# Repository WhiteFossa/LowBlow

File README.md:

# Project LowBlow - Advanced programmable cooler controller

Open source and hardware (GPLv3+) advanced programmable cooler controller.

## Features
- Automatically learns cooler characteristics: at power on it determines minimal voltage at one cooler starts, minimal RPMs and maximal RPMs, so you don't need to adjust temperature-to-RPMs settings for different coolers;
- Cooler speed is being controlled via RPMs loopback (using tachometer), so 50% RPMs will actually be 50% RPMs, not just a half of power voltage. In addition if something affects cooler RPMs, voltage will be adjusted to keep desired RPMs.
- Control tool to configure temperature-to-RPMs curve. Using this tool you can set up curve via changing values in table, view how curve looks and finally generate EEPROM HEX file to flash it into controller.

Control tool screenshot:

## How to build/flash/use etc
Each project directory (i.e. Hardware, Firmware and Control Tool) contain README file with instructions.

## License
Everything in this project (except Intel HEX library) are distributed under GPLv3 or later version license.

Intel HEX library is written by  Kimmo Kulovesi, distributed under MIT license and can be downloaded from here: https://github.com/arkku/ihex

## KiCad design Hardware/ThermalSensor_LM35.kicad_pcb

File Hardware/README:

Project LowBlow control tool.
https://github.com/WhiteFossa/LowBlow

Hardware README

I. Desolder C8 before flashing (flashing will be unsuccessfull if not desoldered) and solder back before using (without C8 tachometer signal wouldn't be clear and device may not work).

II. Project depends on my components for KiCAD library, you can download it here: https://github.com/WhiteFossa/fossas_kicad_lib

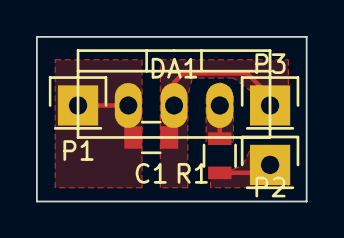
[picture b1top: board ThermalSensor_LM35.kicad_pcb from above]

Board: 2 copper layers, 15.0 x 9.1 mm, 6 parts (0 on the bottom side), 4 nets.

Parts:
C1: 0.1uF; C_0805
DA1: LM35_-_TO-220; TO-220_Neutral123_Vertical
P1: VCC; Pin_Header_Straight_1x01
P2: OUT; Pin_Header_Straight_1x01
P3: GND; Pin_Header_Straight_1x01
R1: 2k; R_0805

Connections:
unnamed: C1.1, DA1.1, P1.1
unnamed: C1.2, DA1.2, P3.1
unnamed: DA1.3, R1.2
unnamed: P2.1, R1.1

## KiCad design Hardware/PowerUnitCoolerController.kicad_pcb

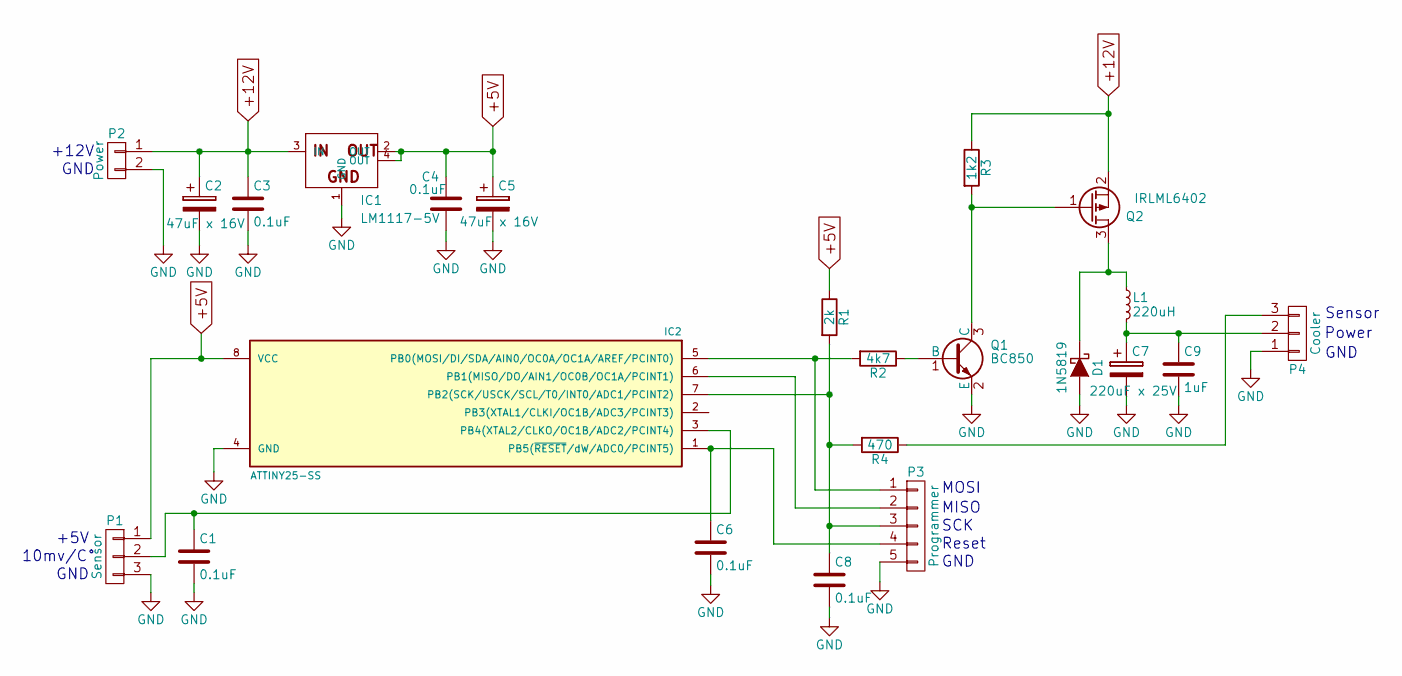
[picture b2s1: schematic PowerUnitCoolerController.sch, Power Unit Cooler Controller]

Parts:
C1, C3, C4, C6, C8: 0.1uF; C_0805
C2, C5: 47uF x 16V; TantalC_SizeV_EIA-7343
C7: 220uF x 25V; c_elec_8x10.5
C9: 1uF; C_0805
D1: 1N5819; MiniMELF_Handsoldering
IC1: LM1117-5V; SOT-223
IC2: ATTINY25-SS; SOIJ-8_5.3x5.3mm_Pitch1.27mm
L1: 220uH; Neosid_Inductor_SM-NE56_SMD2220
P1: Sensor; Pin_Header_Straight_1x03
P2: Power; Pin_Header_Straight_1x02
P3: Programmer; Pin_Header_Straight_1x05
P4: Cooler; Pin_Header_Straight_1x03
Q1: BC850; SOT-23
Q2: IRLML6402; SOT-23
R1: 2k; R_0805
R2: 4k7; R_0805
R3: 1k2; R_0805
R4: 470; R_0805

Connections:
+5V: C4.1, C5.1, IC1.2 (OUT), IC1.4 (OUT), IC2.8 (VCC), P1.1, R1.1
+12V: C2.1, C3.1, IC1.3 (IN), P2.1, Q2.2 (S), R3.1
GND: C1.2, C2.2, C3.2, C4.2, C5.2, C6.2, C7.2, C8.2, C9.2, D1.2 (A), IC1.1 (GND), IC2.4 (GND), P1.3, P2.2, P3.5, P4.1, Q1.2 (E)
unnamed: C1.1, IC2.3 (PB4(XTAL2/CLKO/OC1B/ADC2/PCINT4)), P1.2
unnamed: C6.1, IC2.1 (PB5(~RESET~/dW/ADC0/PCINT5)), P3.4
unnamed: C7.1, C9.1, L1.2, P4.2
unnamed: C8.1, IC2.7 (PB2(SCK/USCK/SCL/T0/INT0/ADC1/PCINT2)), P3.3, R1.2, R4.2
unnamed: D1.1 (K), L1.1, Q2.3 (D)
unnamed: IC2.5 (PB0(MOSI/DI/SDA/AIN0/OC0A/OC1A/AREF/PCI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), P3.1, R2.2
unnamed: IC2.6 (PB1(MISO/DO/AIN1/OC0B/OC1A/PCINT1)), P3.2
unnamed: P4.3, R4.1
unnamed: Q1.1 (B), R2.1
unnamed: Q1.3 (C), Q2.1 (G), R3.2

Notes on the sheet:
Sensor
Power
GND
+12V
10mv/C°
+5V
MOSI
MISO
SCK
Reset

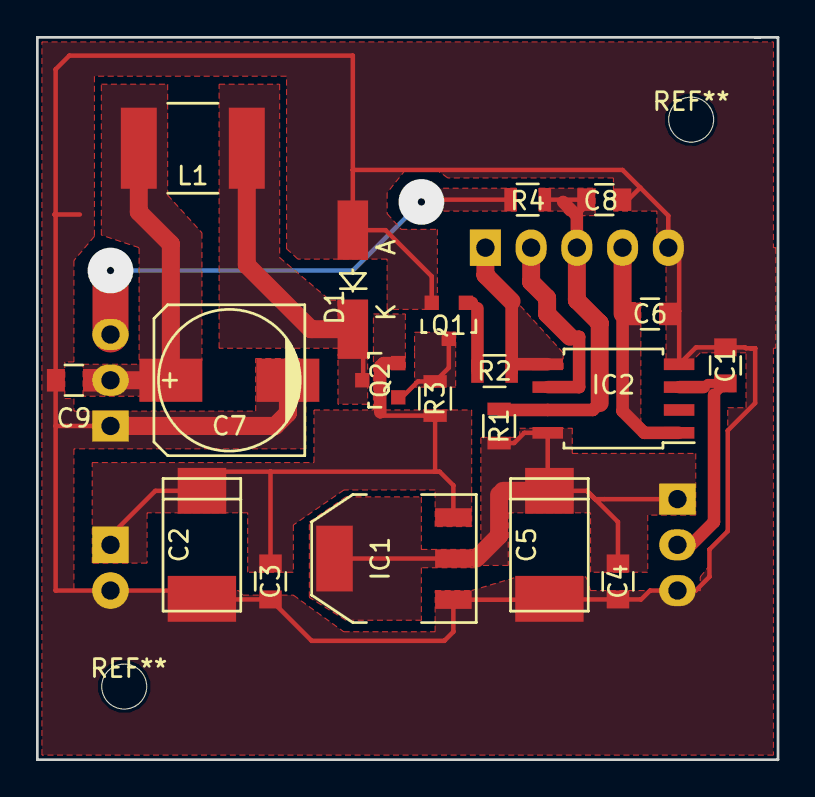
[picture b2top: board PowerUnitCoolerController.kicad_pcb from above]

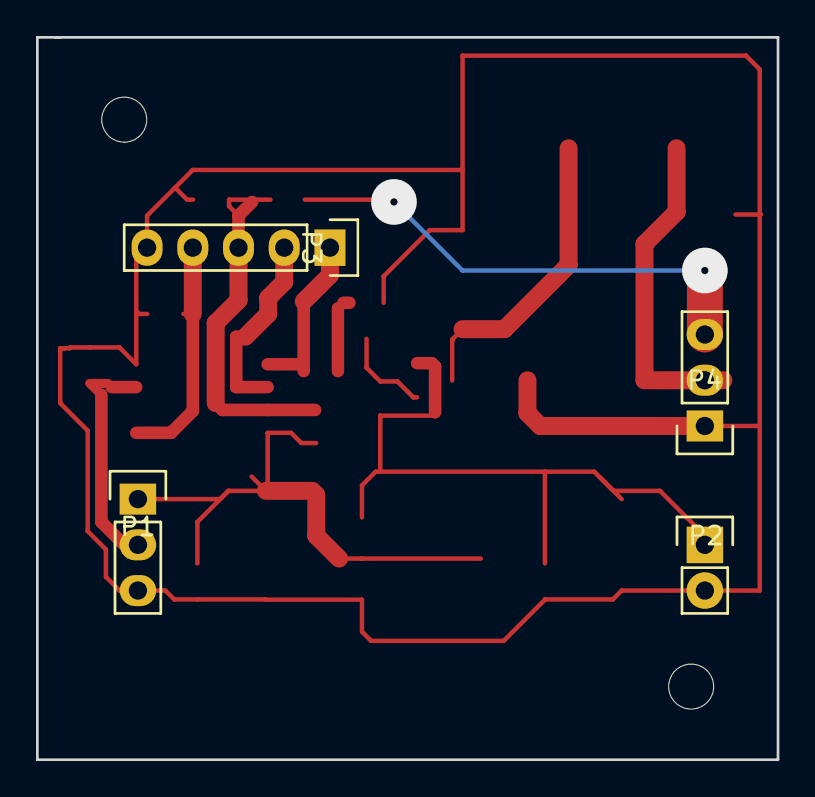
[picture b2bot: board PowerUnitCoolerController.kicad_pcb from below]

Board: 2 copper layers, 41.1 x 40.1 mm, 23 parts (4 on the bottom side), 13 nets.

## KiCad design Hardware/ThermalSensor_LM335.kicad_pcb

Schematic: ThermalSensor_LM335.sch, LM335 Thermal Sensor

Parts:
C1: 0.1uF; C_0805
DA1: LM335; TO-92_Molded_Narrow_Oval
P1: VCC; Pin_Header_Straight_1x01
P2: OUT; Pin_Header_Straight_1x01
P3: GND; Pin_Header_Straight_1x01
R1: 4k7; R_0805
R2: 10k; R_0805
R3: 20k; R_0805

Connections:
unnamed: C1.1, P1.1, R1.1
unnamed: C1.2, DA1.3, P3.1, R3.2
unnamed: DA1.2, R1.2, R2.1
unnamed: P2.1, R2.2, R3.1

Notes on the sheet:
6.(6) mV/°K 0°C -> 1.82V 100°C -> 2.49V

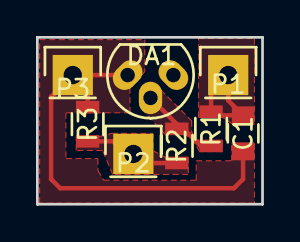
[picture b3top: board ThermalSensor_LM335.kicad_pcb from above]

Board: 2 copper layers, 12.5 x 9.3 mm, 8 parts (0 on the bottom side), 4 nets.

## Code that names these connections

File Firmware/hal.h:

/*
	This file is part of Power Unit Cooler Controller firmware.

	Power Unit Cooler Controller firmware is free software:
	you can redistribute it and/or modify it under the terms of the
	GNU General Public License as published by the Free Software
	Foundation, either version 3 of the License, or (at your option)
	any later version.

	Power Unit Cooler Controller firmware is distributed in the hope
	that it will be useful, but WITHOUT ANY WARRANTY; without even
	the implied warranty of MERCHANTABILITY or FITNESS FOR A
	PARTICULAR PURPOSE.  See the GNU General Public License for more
	details.

	You should have received a copy of the GNU General Public License
	along with Notebook Cooler Controller firmware.

	If not, see <http://www.gnu.org/licenses/>.

	-------------------------------------------------------------------------

	hal.h

	Hardware abstraction layer header file.

	Part of "LowBlow" project.

	Created 2016/02/07 by White Fossa, also known as Artyom Vetrov.

	Feel free to contact: whitefossa@gmail.com

	Repository: https://github.com/WhiteFossa/LowBlow

	If repository above is not available, try my LiveJournal:
	fossa-white.livejournal.com

	or as last measure try to search for #WhiteFossa hashtag.

	-------------------------------------------------------------------------
 */

#ifndef HAL_H_
#define HAL_H_

/**
 * Hardware:
 *
 *                             ATTINY25
 *                           +----__----+
 * RESET (PB5)          ->---| 1      8 |-----     VCC
 * NOT CONNECTED		->---| 2      7 |---<-     TACHO	(INT0/PB2)
 * TSENS (ADC2/PB4)     ->---| 3      6 |---<-     NOT CONNECTED
 * GND                  -----| 4      5 |--->-     PWM		(PB0/OC0A)
 *                           +----------+
 *
 * Directions:
 * PIN		DIR		DDRB
 *
 * PB0		OUT		1
 * PB1		IN		0
 * PB2		IN		0
 * PB3		IN		0
 * PB4		IN		0
 * PB5		IN		0
 *
 *
 * We can use two kinds on thermal sensors:
 *
 * 1) LM35 in direct mode, i.e. 10mV/°C. Uout=0.01*t°. Uncomment USE_LM35_SENSOR if you are using it. ADC will use 1.1V reference,
 * 10-bit mode, so ADC = 9.(309)*t°.
 *
 *   t °C		U V		ADC
 *   0			0		0
 *   100		1		233
 *
 * 233 steps per 100°C
 *
 * 2) LM335 with 2/3 divider, i.e. 6.(6)mV/°K. Uout=2*(t°+273.15)/300. ADC will use 2.56V reference, 10-bit moide. ADC=2.(6)*t°+728.4
 *
 *   t °C		U V		ADC
 *   0		   1.821	728
 *   100       2.487	995
 *
 * 267 steps per 100°C
 *
 * t° is temperature in Celsius.
 */

/**
 * !!!!!!!!!!!!!!!!!!!!!!!!!!!!!!!!!!!!!!!!!!!!!!!!!!
 * !!!!!!! UNCOMMENT IT IF LM35 SENSOR USED !!!!!!!!!
 * !!!!!!!!!!!!!!!!!!!!!!!!!!!!!!!!!!!!!!!!!!!!!!!!!!
 * #define USE_LM35_SENSOR
 */


/* AVR Libc includes*/
#include <avr/io.h> /* Common */
#include <avr/wdt.h> /* Watchdog timer */
#include <avr/interrupt.h> /* Interrupts support */
#include <util/delay_basic.h> /* Basic delays */

/* Macros */


/* Get cooler duty cycle */
#define hal_get_cooler_duty_cycle() OCR0A


/* End of macros */

/* Constants */

/**
 *  MCU Frequency
 */
#define F_CPU 8000000UL

/** !!!!!!!!!!!!!!!!!!!!!!!!!!!!!!!!!!!!!!!!!!!!!!!!!!!!!!!!!!
 *  !!PORTS DIRECTIONS - WRONG SETTINGS WILL DAMAGE HARDWARE!!
 *  !!!!!!!!!!!!!!!!!!!!!!!!!!!!!!!!!!!!!!!!!!!!!!!!!!!!!!!!!!
 */
#define HAL_PORTB_DIR 0b00000001

/**
 * Port, where cooler connected
 */
#define HAL_COOLER_PORT PORTB

/**
 * Cooler connected here
 */
#define HAL_COOLER_PIN 0x00 /* PB0 */

/**
 *  Watchdog timeout interval
 */
#define HAL_WDT_INTERVAL WDTO_2S

/**
 * Minimal possible duty cycle (set cycle to it to stop cooler).
 */
#define HAL_MIN_DUTY_CYCLE 0x00

/**
 * Maximal possible duty cycle
 */
#define HAL_MAX_DUTY_CYCLE 0xFF

/* This number of Timer1 overflows is near equal to 1 second
 * clock = 8.0 MHz, prescaler 16384, overflow occurs 8000000 / (16384 * 256) ~ 2 times per second.
 */
#define HAL_TIMER1_OVERFLOWS_PER_SECOND 2

/**
 * Number of bits, to what hal_adc_accumulator need to be shifted left to get hal_temperature.
 */
#define HAL_ADC_RESULT_SHIFT_BITS 8

/**
 * How many ADC measurements will be averaged to get temperature MINUS ONE (to keep it within uint8_t)
 */
#define HAL_ADC_NUM_OF_MEASUREMENTS (1 << HAL_ADC_RESULT_SHIFT_BITS) - 1

/* Flags */

/**
 *  Raised on exit from hal_second_tick() function. Can be used to know that new tachometer measurement completed
 */
#define HAL_F0_JUST_TICKED 0

/* End of flags */

/* End of constants */



/* Variables */

/**
 * Variable for different flags, related to HAL. By default all flags are cleared (zeros).
 */
volatile uint8_t hal_flags0;

/* Loaded with HAL_TIMER1_OVERFLOWS_PER_SECOND on hal_second_tick() and decreases on every Timer1 interrupt. If this
 * variable equals 0 AFTER decrement then new second passed, calling hal_second_tick()
 */
volatile uint16_t hal_timer1_overflows_number;

/** Increases with every pulse from tachometer (i.e. INT0), gets copied to hal_tacho when hal_second_tick() called and
 * set to 0. For most coolers 2 pulses from tachometer = 1 revolution, but as I heard some coolers with 8 pulses per
 * revolution exists.
 * With uint16_t, 8 pulses per revolution and 1 second interval maximal allowed RPM will be 65535 * 60 / 8 = 491512.5
 */
volatile uint16_t hal_tacho_counter;

/** Number of tachometer pulses per second
 */
volatile uint16_t hal_tacho;

/**
 * ADC measurements accumulating here before being averaged and placed into hal_temperature.
 */
volatile uint32_t hal_adc_accumulator;

/**
 * Counter to count ADC measurements.
 */
volatile uint8_t hal_adc_avg_counter;


/**
 * Averaged ADC measurement, i.e. temperature.
 */
volatile uint16_t hal_temperature;

/* End of variables */


/* Functions prototypes */

/** Very early initialization stage. Here we have to disable interrupts ad set-up watchdog to avoid reset during
 * initialization.
 */
void hal_early_init(void) __attribute__((naked)) __attribute__((section(".init3")));

/**
 * Hardware initialization function. Call it before any other functions.
 */
void hal_init();

/** Set PWM duty cycle. If cycle > HAL_MAX_DUTY_CYCLE then set to HAL_MAX_DUTY_CYCLE.
 * If cycle < HAL_MIN_DUTY_CYCLE then set it to HAL_MIN_DUTY_CYCLE.
 *
 * Setting duty cycle to HAL_MIN_DUTY_CYCLE will lead to cooler stop.
 *
 * @param cycle Duty cycle from HAL_MIN_DUTY_CYCLE to HAL_MIN_DUTY_CYCLE
 */
void hal_set_cooler_duty_cycle(int16_t cycle);

/**
 * Gets called every second
 */
void hal_second_tick();

/**
 * Call this function to stop cooler (PWM will be disabled, PWM output (PB0) will be held in 0).
 */
void hal_stop_cooler();

/**
 * Call this function to start cooler (PWM will be enabled, using last set PWM duty cycle).
 */
void hal_start_cooler();

/* End of function prototypes */

#endif /* HAL_H_ */

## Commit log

2017-09-12 Moved from my local repository.
2017-09-24 GPL headers added
2017-09-24 Tabluation fixed; Settings saver/loader beginned.
2017-10-06 Interface for settings Saver/Loader.
2017-10-06 Skeleton for settings saver/loader.
2017-10-06 Updated doxygen documentation.
2017-10-22 Before starting to use ADC->Temperature convertor from SettingsSaverLoader.
2017-10-26 Now using ADC->Temperature convertor from settings saver/loader.
2017-10-26 Switched to settings generator from settings saver/loader.
2017-10-26 Updated doxygen documentation
2017-11-12 - Support for Save and Save As; - Some refactoring (removed obsoleted trUtf8).
2017-12-17 - Fixed crash on Cancel in dialog for new file creation.
2018-01-02 Now base temperature and RPM level can be loaded from file.
2018-01-27 Now we can save and load settings, but some refactoring is still needed on it.
2018-01-27 Now settings file type and version are being checked on load.
2018-01-28 Some refactoring on AdcTemperatureConvertor, related to saving and loading settings.
2018-02-18 Refactored settings loader in ADC -> Temperature convertor.
2018-02-18 Now "modified" mark is being set almost correctly.
2018-02-18 Doxygen documentation updated.
2018-03-04 - Now marking file as modified work correctly; - Some refactoring in MainWindow.
2018-03-08 - Some refactoring; - Started to work on Settings-to-EEPROM generator.
2018-03-10 - Partially done with export to EEPROM (now we need Intel HEX library); - Some refactoring; - Eradicated all warnings; - Doxygen documentation regenerated.
2018-08-26 -Migrated to Qt5
2018-08-28 Now we can export data to EEPROM
2018-08-28 Fixed bug with non-zero ADC delta in zero step.
2018-08-28 Fixed TODO in simple graph implementation.
2018-08-28 Seems that PC control tool is ready
2018-08-28 - Now it seems that firmware is ready - Updated doxygen documentation for firmware
2018-08-28 Fixed bug with ADC delta
2018-08-28 Some refactoring
2018-08-28 Added keyboard shortcuts
2018-08-29 Fixed SEGFAULT on settings open.
2018-08-29 Fixed bug with incorrect base temperature in EEPROM.
2018-08-29 Fixed bugs in firmware
2018-08-30 - Some refactoring in firmware - Updated firmware documentation
2018-09-02 Updated headers in Firmware files
2018-09-02 Updated headers for control tool
2018-09-02 Added hints for new file creation
2018-09-15 Added "about" dialogue.
2018-09-15 Updated Doxygen documentation for control tool
2018-09-15 Added README for control tool
2018-10-06 - Added readme for firmware and hardware
2018-10-06 Final README
2018-10-06 Updated README and Doxygen files.
2018-10-06 Added control tool screenshot
2018-10-06 Modified README to include screenshot
2018-10-06 Readme grammar

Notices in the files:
Hardware/PowerUnitCoolerController.kicad_pcb:
Licence: GPLv3+
